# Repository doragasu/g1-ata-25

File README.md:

# g1-ata-25
G1-ATA interface for embedding 2.5" ATA hard disks inside the Dreamcast console

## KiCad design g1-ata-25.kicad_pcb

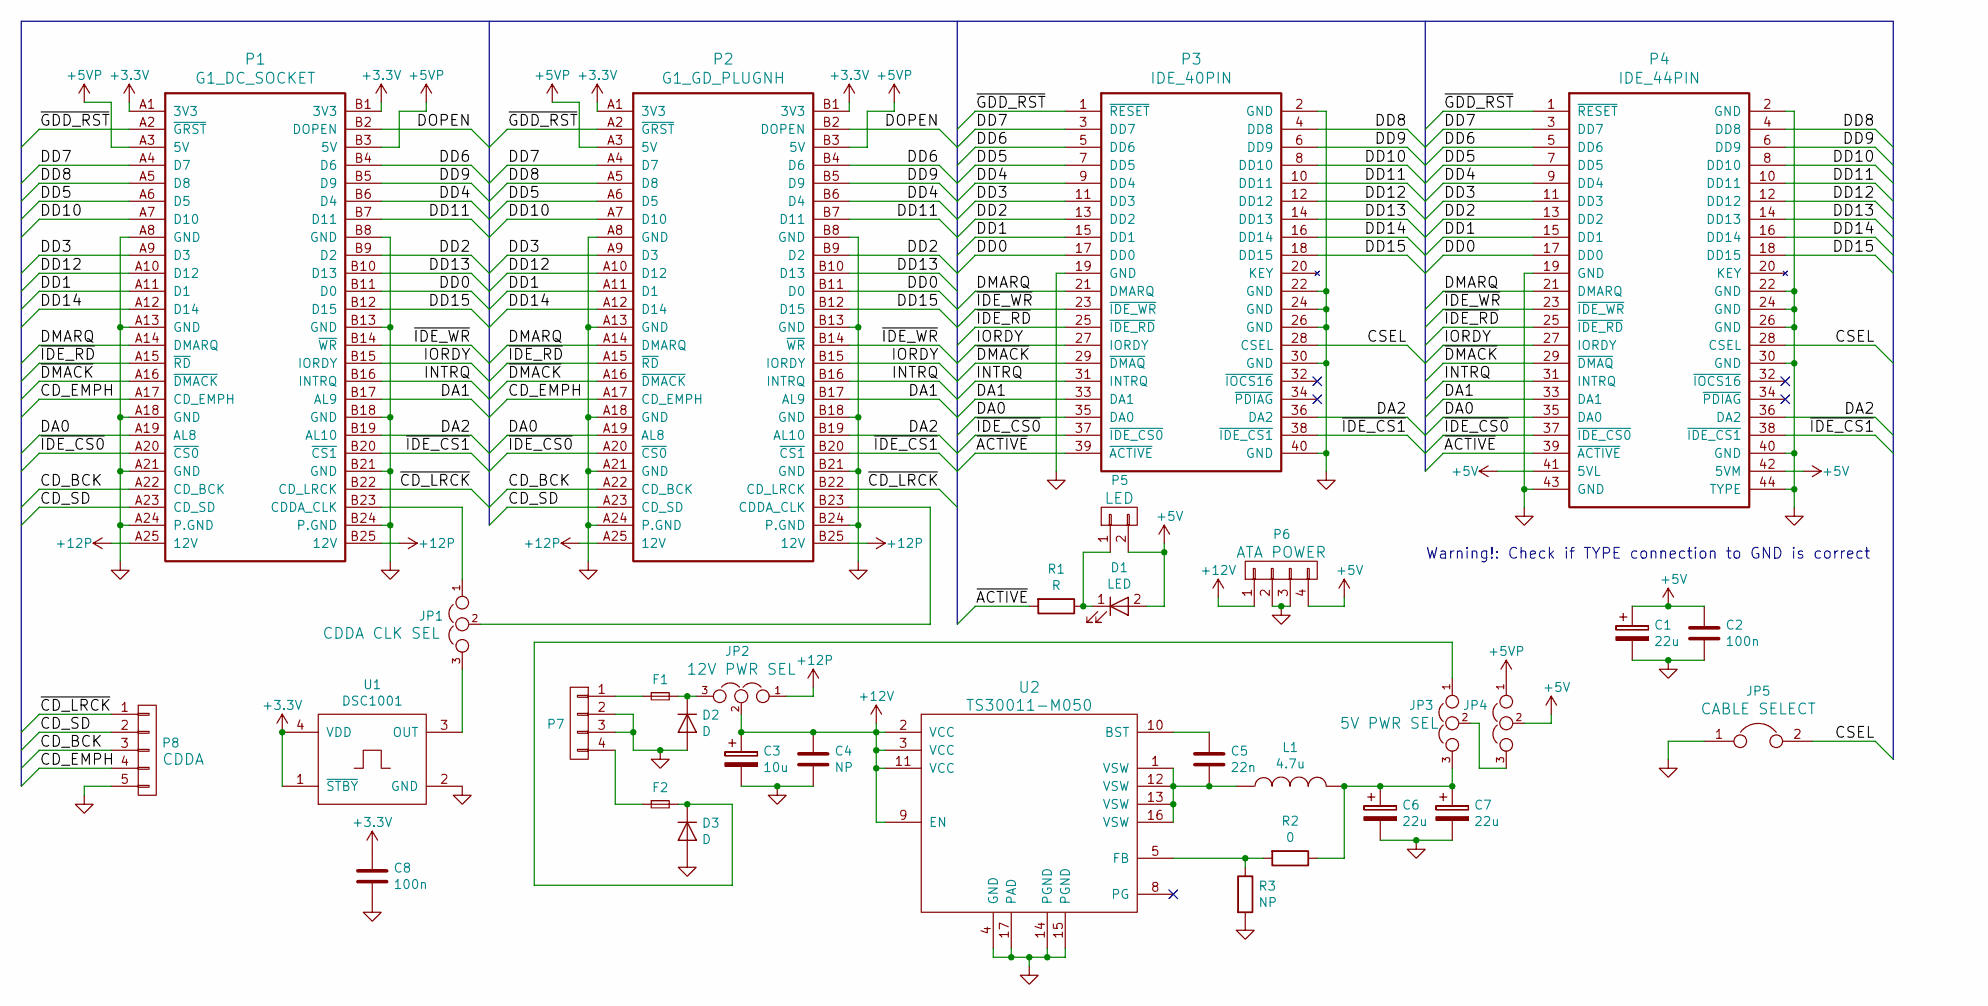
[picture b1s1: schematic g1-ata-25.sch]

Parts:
C1, C6, C7: 22u; C_1206
C2, C8: 100n; C_0805
C3: 10u; C_0805
C4: NP; C_0805
C5: 22n; C_0805
D1: LED; LED_0603
D2, D3: D; MiniMELF_Standard
F1, F2: F_Small; C_0805
JP1, JP2, JP3, JP4: JUMPER3; Pin_Header_Straight_1x03
JP5: JUMPER; Pin_Header_Straight_1x02
L1: 4.7u; INDUCTOR-NR4018
P1: G1_DC_SOCKET; MOLEX_53408-0570
P2: G1_GD_PLUGNH; MOLEX_52584-0508
P3: IDE_40PIN; Pin_Header_Straight_2x20
P4: IDE_44PIN; SOCKET_2X22_2MM_ANGLE
P5: CONN_01X02; Socket_MOLEX-KK-RM2-54mm_Lock_2pin_straight
P6, P7: CONN_01X04; Socket_MOLEX-KK-RM3-96mm_Lock_4pin_straight
P8: CONN_01X05; Socket_Strip_Straight_1x05
R1: R; R_0805
R2: 0; R_0805
R3: NP; R_0805
U1: DSC1001; DSC1001-32x25M
U2: TS30011-M050; QFN-16-1EP_3x3mm_Pitch0.5mm

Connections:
+3V3: C8.1, P1.A1 (3V3), P1.B1 (3V3), P2.A1 (3V3), P2.B1 (3V3), U1.1 (~STBY), U1.4 (VDD)
+5V: C1.1, C2.1, D1.2 (A), JP4.2, P4.41 (5VL), P4.42 (5VM), P5.2, P6.4
+5VP: JP4.1, P1.A3 (5V), P1.B3 (5V), P2.A3 (5V), P2.B3 (5V)
+12P: JP2.1, P1.A25 (12V), P1.B25 (12V), P2.A25 (12V), P2.B25 (12V)
+12V: C3.1, C4.1, JP2.2, P6.1, U2.2 (VCC), U2.3 (VCC), U2.9 (EN), U2.11 (VCC)
/CD_BCK: P1.A22 (CD_BCK), P2.A22 (CD_BCK), P8.3
/CD_EMPH: P1.A17 (CD_EMPH), P2.A17 (CD_EMPH), P8.4
/CD_SD: P1.A23 (CD_SD), P2.A23 (CD_SD), P8.2
/CSEL: JP5.2, P3.28 (CSEL), P4.28 (CSEL)
/DA0: P1.A19 (AL8), P2.A19 (AL8), P3.35 (DA0), P4.35 (DA0)
/DA1: P1.B17 (AL9), P2.B17 (AL9), P3.33 (DA1), P4.33 (DA1)
/DA2: P1.B19 (AL10), P2.B19 (AL10), P3.36 (DA2), P4.36 (DA2)
/DD0: P1.B11 (D0), P2.B11 (D0), P3.17 (DD0), P4.17 (DD0)
/DD1: P1.A11 (D1), P2.A11 (D1), P3.15 (DD1), P4.15 (DD1)
/DD2: P1.B9 (D2), P2.B9 (D2), P3.13 (DD2), P4.13 (DD2)
/DD3: P1.A9 (D3), P2.A9 (D3), P3.11 (DD3), P4.11 (DD3)
/DD4: P1.B6 (D4), P2.B6 (D4), P3.9 (DD4), P4.9 (DD4)
/DD5: P1.A6 (D5), P2.A6 (D5), P3.7 (DD5), P4.7 (DD5)
/DD6: P1.B4 (D6), P2.B4 (D6), P3.5 (DD6), P4.5 (DD6)
/DD7: P1.A4 (D7), P2.A4 (D7), P3.3 (DD7), P4.3 (DD7)
/DD8: P1.A5 (D8), P2.A5 (D8), P3.4 (DD8), P4.4 (DD8)
/DD9: P1.B5 (D9), P2.B5 (D9), P3.6 (DD9), P4.6 (DD9)
/DD10: P1.A7 (D10), P2.A7 (D10), P3.8 (DD10), P4.8 (DD10)
/DD11: P1.B7 (D11), P2.B7 (D11), P3.10 (DD11), P4.10 (DD11)
/DD12: P1.A10 (D12), P2.A10 (D12), P3.12 (DD12), P4.12 (DD12)
/DD13: P1.B10 (D13), P2.B10 (D13), P3.14 (DD13), P4.14 (DD13)
/DD14: P1.A12 (D14), P2.A12 (D14), P3.16 (DD14), P4.16 (DD14)
/DD15: P1.B12 (D15), P2.B12 (D15), P3.18 (DD15), P4.18 (DD15)
/DMARQ: P1.A14 (DMARQ), P2.A14 (DMARQ), P3.21 (DMARQ), P4.21 (DMARQ)
/DOPEN: P1.B2 (DOPEN), P2.B2 (DOPEN)
/INTRQ: P1.B16 (INTRQ), P2.B16 (INTRQ), P3.31 (INTRQ), P4.31 (INTRQ)
/IORDY: P1.B15 (IORDY), P2.B15 (IORDY), P3.27 (IORDY), P4.27 (IORDY)
/~ACTIVE: P3.39 (~ACTIVE), P4.39 (~ACTIVE), R1.2
/~CD_LRCK: P1.B22 (CD_LRCK), P2.B22 (CD_LRCK), P8.1
/~DMACK: P1.A16 (~DMACK), P2.A16 (~DMACK), P3.29 (~DMAQ), P4.29 (~DMAQ)
/~GDD_RST: P1.A2 (~GRST), P2.A2 (~GRST), P3.1 (~RESET), P4.1 (~RESET)
/~IDE_CS0: P1.A20 (~CS0), P2.A20 (~CS0), P3.37 (~IDE_CS0), P4.37 (~IDE_CS0)
/~IDE_CS1: P1.B20 (~CS1), P2.B20 (~CS1), P3.38 (~IDE_CS1), P4.38 (~IDE_CS1)
/~IDE_RD: P1.A15 (~RD), P2.A15 (~RD), P3.25 (~IDE_RD), P4.25 (~IDE_RD)
/~IDE_WR: P1.B14 (~WR), P2.B14 (~WR), P3.23 (~IDE_WR), P4.23 (~IDE_WR)
GND: C1.2, C2.2, C3.2, C4.2, C6.2, C7.2, C8.2, D2.2 (A), D3.2 (A), JP5.1, P1.A8 (GND), P1.A13 (GND), P1.A18 (GND), P1.A21 (GND), P1.A24 (P.GND), P1.B8 (GND), P1.B13 (GND), P1.B18 (GND), P1.B21 (GND), P1.B24 (P.GND), P2.A8 (GND), P2.A13 (GND), P2.A18 (GND), P2.A21 (GND), P2.A24 (P.GND), P2.B8 (GND), P2.B13 (GND), P2.B18 (GND), P2.B21 (GND), P2.B24 (P.GND), P3.2 (GND), P3.19 (GND), P3.22 (GND), P3.24 (GND), P3.26 (GND), P3.30 (GND), P3.40 (GND), P4.2 (GND), P4.19 (GND), P4.22 (GND), P4.24 (GND), P4.26 (GND), P4.30 (GND), P4.40 (GND), P4.43 (GND), P4.44 (TYPE), P6.2, P6.3, P7.2, P7.3, P8.5, R3.2, U1.2 (GND), U2.4 (GND), U2.14 (PGND), U2.15 (PGND), U2.17 (PAD)
unnamed: C5.1, U2.10 (BST)
unnamed: C5.2, L1.1, U2.1 (VSW), U2.12 (VSW), U2.13 (VSW), U2.16 (VSW)
unnamed: C6.1, C7.1, JP3.3, L1.2, R2.1
unnamed: D1.1 (K), P5.1, R1.1
unnamed: D2.1 (K), F1.2, JP2.3
unnamed: D3.1 (K), F2.2, JP3.1
unnamed: F1.1, P7.1
unnamed: F2.1, P7.4
unnamed: JP1.1, P1.B23 (CDDA_CLK)
unnamed: JP1.2, P2.B23 (CDDA_CLK)
unnamed: JP1.3, U1.3 (OUT)
unnamed: JP3.2, JP4.3
unnamed: R2.2, R3.1, U2.5 (FB)

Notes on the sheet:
Warning!: Check if TYPE connection to GND is correct

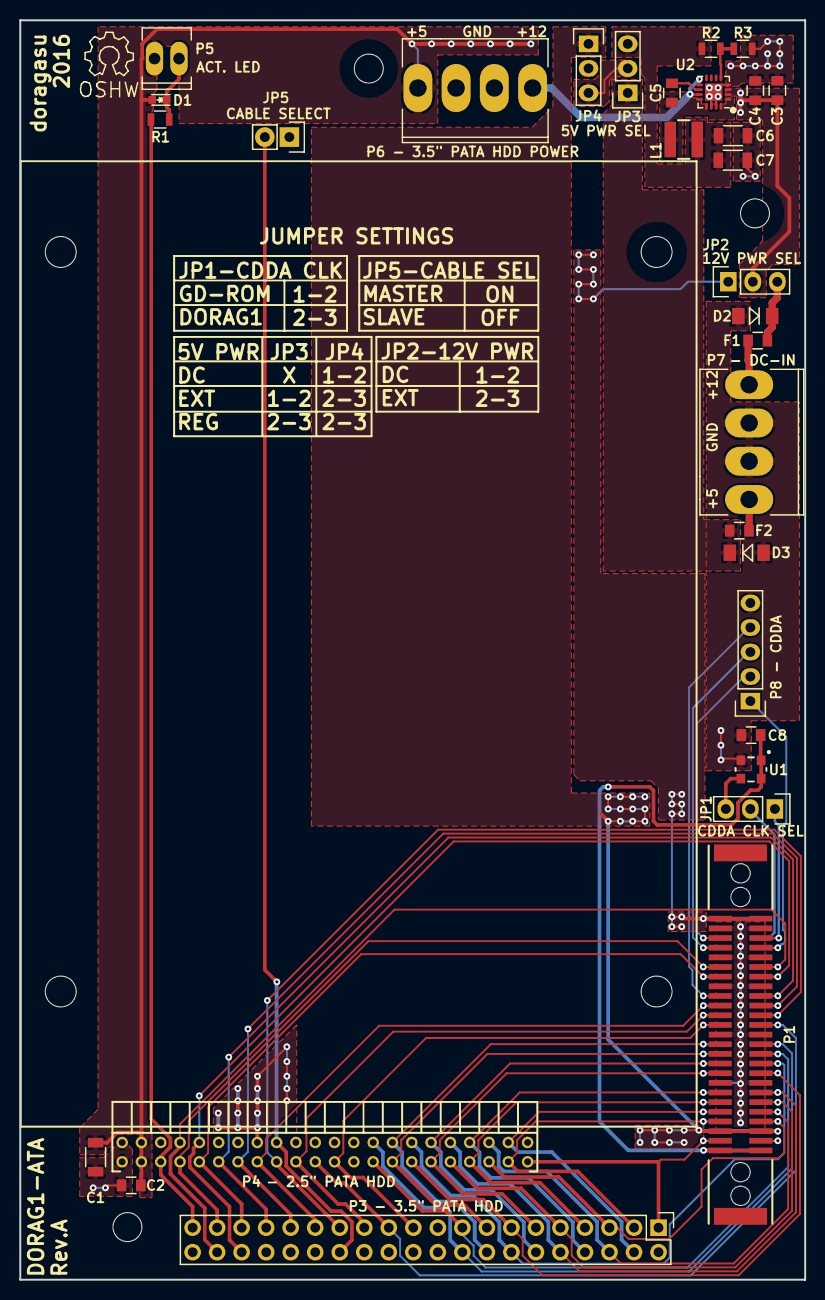
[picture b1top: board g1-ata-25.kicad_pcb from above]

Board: 2 copper layers, 81.3 x 130.4 mm, 36 parts (1 on the bottom side), 54 nets.

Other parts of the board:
MountingHole_3mm, MountingHole_3mm#2, MountingHole_3mm#3: VAL**; MountingHole_3mm
Symbol_OSHW-Logo_SilkScreen: VAL**; Symbol_OSHW-Logo_SilkScreen

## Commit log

2016-05-29 Initial commit.
2016-05-30 Added IDE connectors and enhanced g1-dc-socket numbering.
2016-05-30 Wired connectors.
2016-05-31 Added LED and connectors, wired some more elements.
2016-05-31 Schematic almost finished (just needs a revision).
2016-06-01 First test placing components.
2016-06-01 Moved some components.
2016-06-03 Routing...
2016-06-08 Routing almost finished.
2016-06-08 Small routing tweaks to power linea mainly. Also added HDD holes.
2016-06-09 Added an external 5V power source plus other tweaks.
2016-06-09 Added fuse + polarity protection for 5V input (not yet routed).
2016-06-09 Added jumper settings tables on silk screen.
2016-06-10 Added OSHW symbol and some more tiny teaks to silk screen.
2016-07-04 Modified Gerber generation parameters.
2017-02-05 Added bootstrap capacitor value.
2017-09-24 Fixed connection to pass CDDA_CLK from GD-ROM drive.

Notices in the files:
g1-ata-25.sch:
License: TBD
